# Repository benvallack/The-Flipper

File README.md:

# The-Flipper

KiCad and Gerber files for this quirky 28 key split keyboard. 

Created using the amazing Ergogen tool: https://github.com/mrzealot/ergogen

This particular version hasn’t been tested yet but a previous very similiar verison worked fine. 

Components: 

Reset switch: https://www.aliexpress.com/item/33013562004.html?spm=a2g0s.9042311.0.0.19f74c4dc7gN7e

Slider switch: https://www.aliexpress.com/item/4000685483225.html?spm=a2g0s.9042311.0.0.19f74c4dc7gN7e

Keymap: https://github.com/benvallack/zmk-config-flipper

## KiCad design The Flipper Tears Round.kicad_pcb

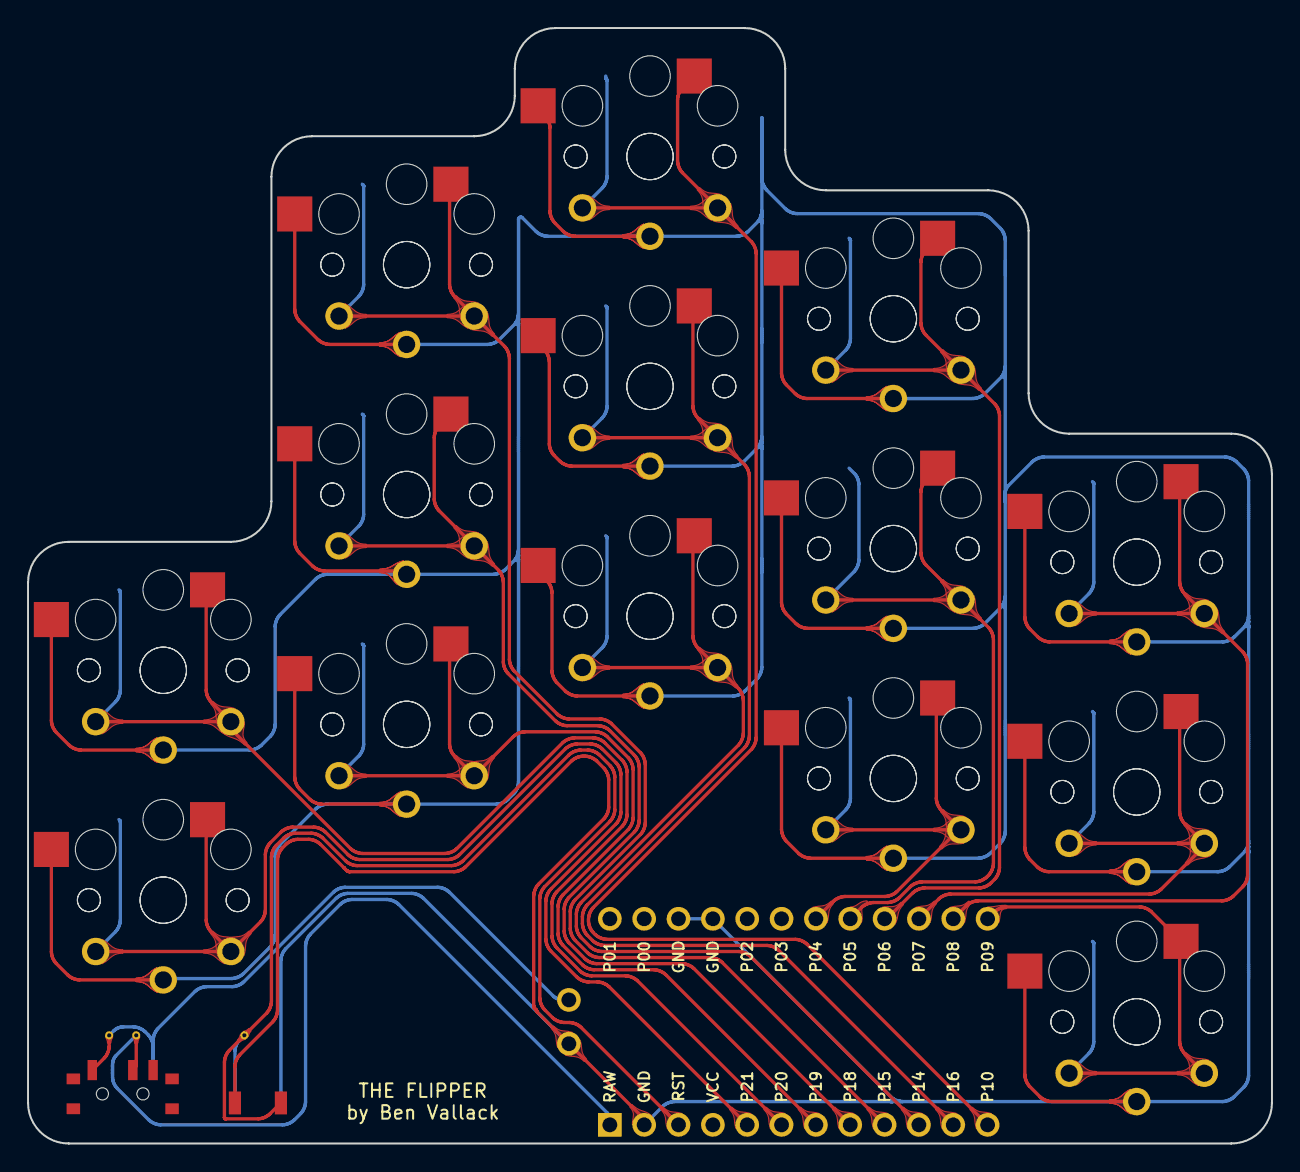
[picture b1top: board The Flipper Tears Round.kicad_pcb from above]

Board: 2 copper layers, 92.0 x 82.5 mm, 29 parts (0 on the bottom side), 15 nets.

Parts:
MCU1: ProMicro
S1, S2, S3, S4, S5, S6, S7, S8, S9, S10, S11, S12, S13, S14, S15, S16, S17, S18, S19, S20, S21, S22, S23, S24, S25, S26, S27, S28: PG1350

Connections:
GND: MCU1.2, MCU1.15, MCU1.16, S1.2, S2.2, S3.2, S4.2, S5.2, S6.2, S7.2, S8.2, S9.2, S10.2, S11.2, S12.2, S13.2, S14.2, S15.2, S16.2, S17.2, S18.2, S19.2, S20.2, S21.2, S22.2, S23.2, S24.2, S25.2, S26.2, S27.2, S28.2
P4: MCU1.19, S17.1, S18.1
P5: MCU1.20, S19.1, S20.1
P6: MCU1.21, S21.1, S22.1
P7: MCU1.22, S25.1, S26.1
P8: MCU1.23, S27.1, S28.1
P9: MCU1.24, S23.1, S24.1
P10: MCU1.12, S15.1, S16.1
P14: MCU1.10, S11.1, S12.1
P15: MCU1.9, S9.1, S10.1
P16: MCU1.11, S13.1, S14.1
P18: MCU1.8, S7.1, S8.1
P19: MCU1.7, S5.1, S6.1
P20: MCU1.6, S3.1, S4.1
P21: MCU1.5, S1.1, S2.1
